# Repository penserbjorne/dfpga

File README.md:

#dfpga

##Fork

- Fork de [Nick Johnson a.k.a. Arachnid](https://github.com/Arachnid/dfpga)
- Fuente del articulo en el [Blog de Nick](http://blog.notdot.net/2012/10/Build-your-own-FPGA)

##Descripción

Implementación de una celda (slice) de un FPGA completamente con lógica 
discreta (componentes de la serie 7400), y un compilador para un dialecto HDL
 personalizado para la misma.

- discretefpga.brd y discretefpga.sch son los archivos para la tarjeta y el 
  esquematico en Eagle.
- dhdl.py es el compilador HDL; para ejecutarlo ``python dhdl.py infile outfile``.
- Los archivos *.dhdl son scripts DHDL de ejemplo.

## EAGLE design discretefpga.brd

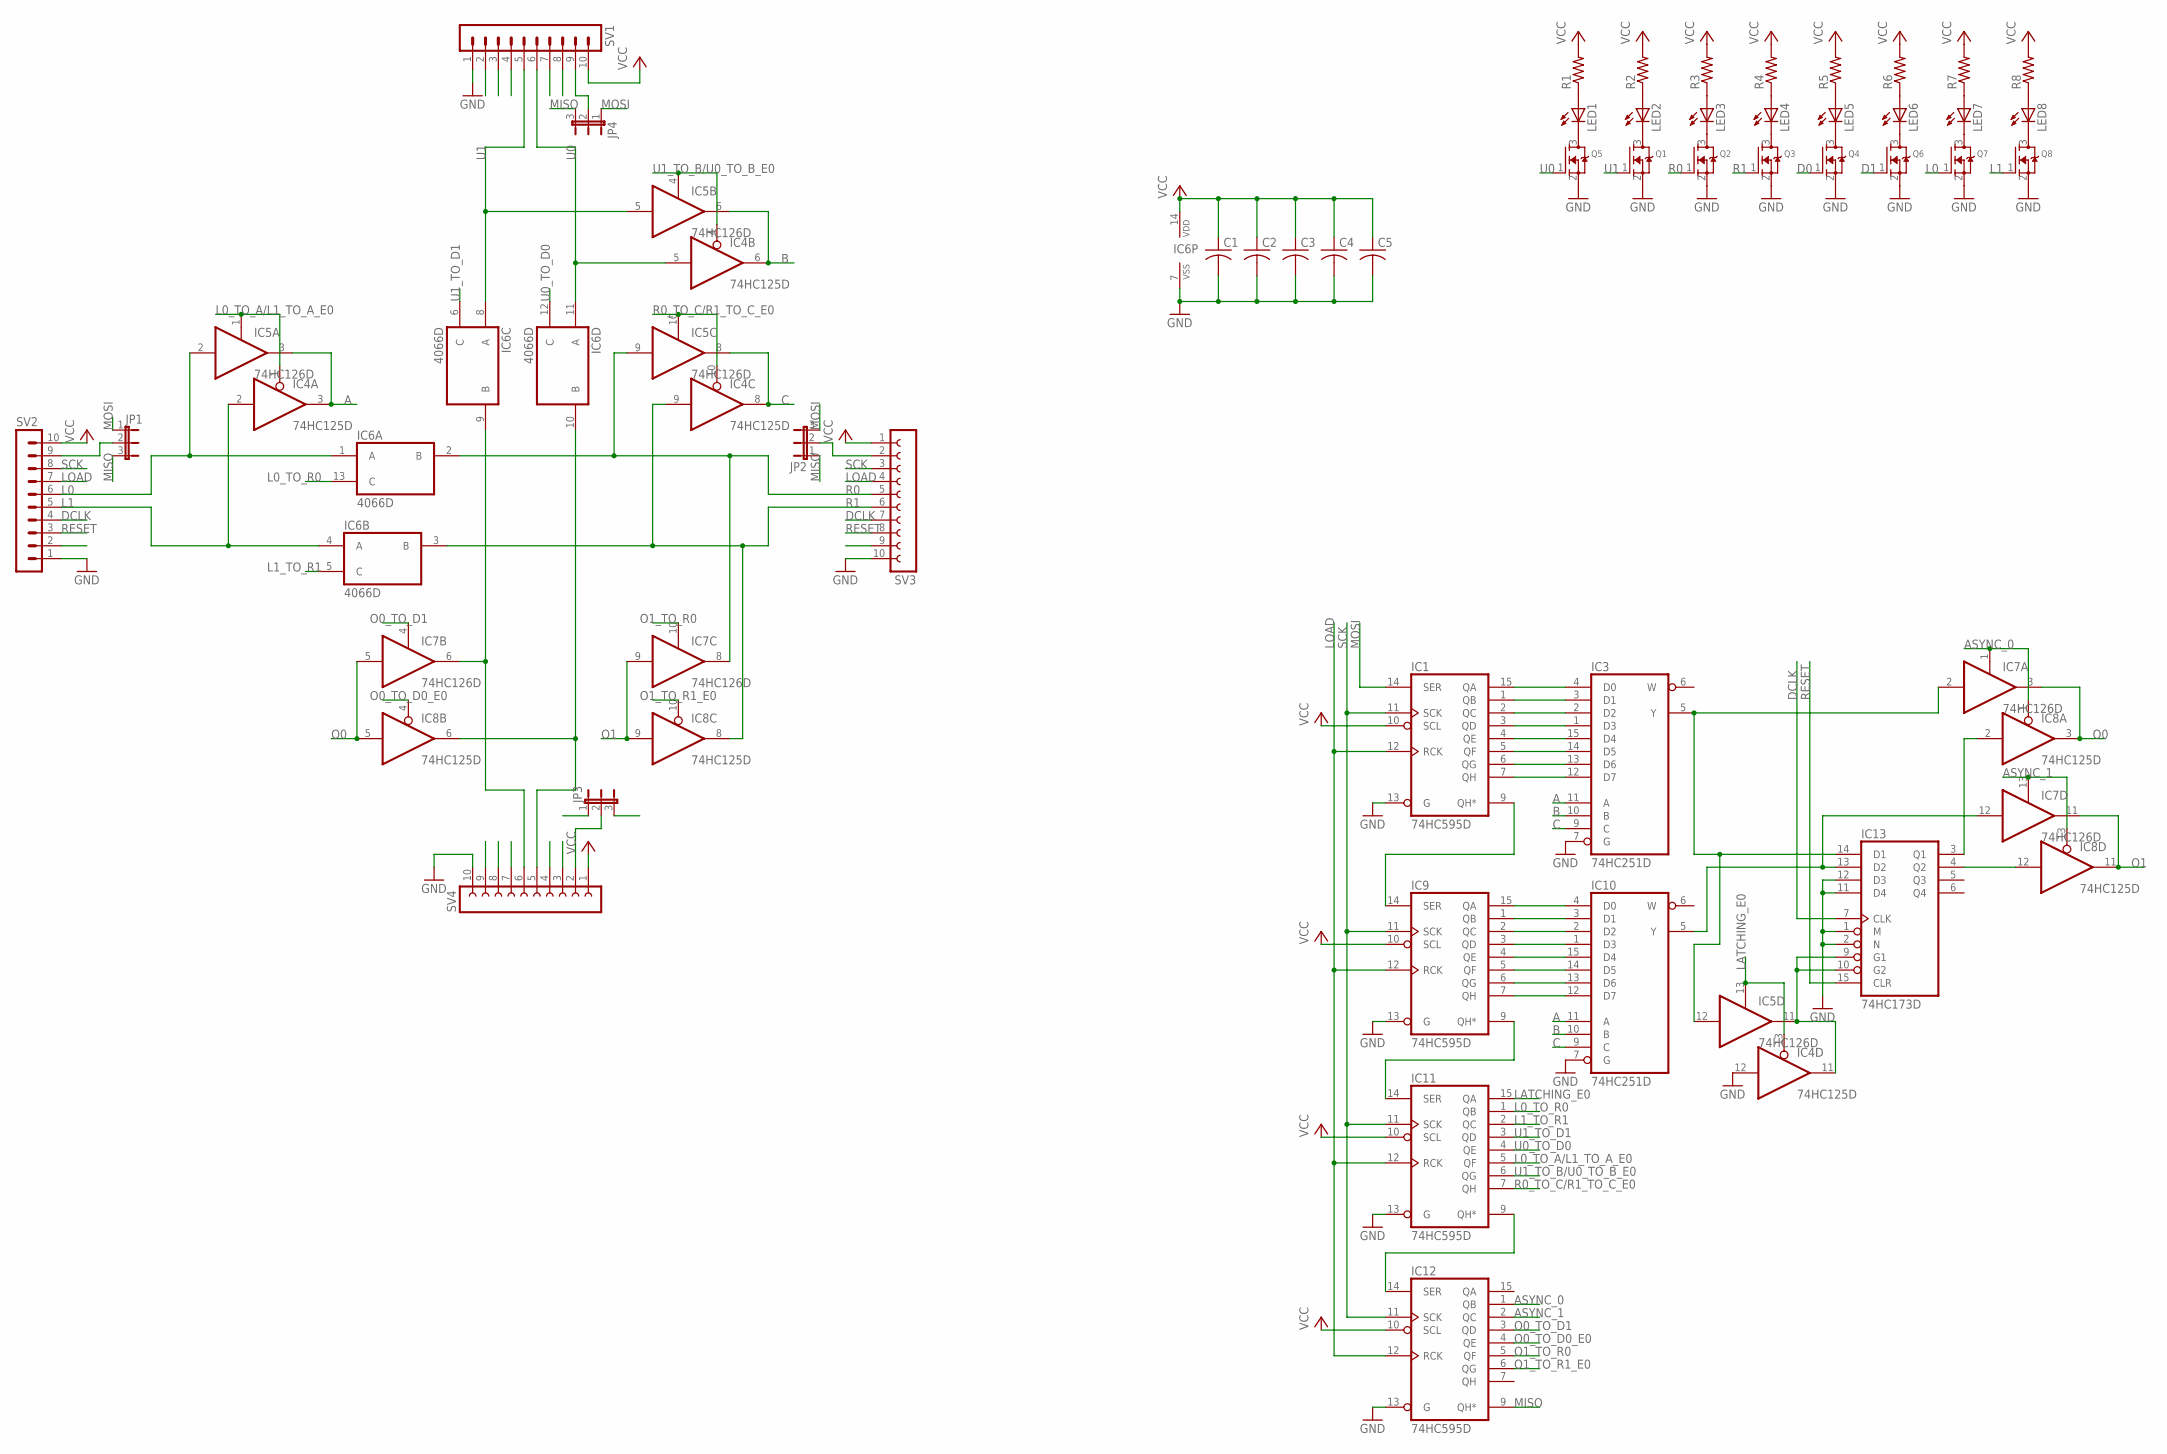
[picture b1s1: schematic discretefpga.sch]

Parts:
C1, C2, C3, C4, C5: C-USC0805; C0805
IC1, IC9, IC11, IC12: 74HC595D; SO16
IC3, IC10: 74HC251D; SO16
IC4, IC8: 74HC125D; SO14
IC5, IC7: 74HC126D; SO14
IC6: 4066D; SO14
IC13: 74HC173D; SO16
JP1, JP2, JP3, JP4: JP2E; JP2
LED1, LED2, LED3, LED4, LED5, LED6, LED7, LED8: LEDCHIP-LED0805; CHIP-LED0805
Q1, Q2, Q3, Q4, Q5, Q6, Q7, Q8: MOSFET-NREFLOW; SOT23
R1, R2, R3, R4, R5, R6, R7, R8: R-US_R0805; R0805
SV1, SV2: MA10-1W
SV3, SV4: FE10W

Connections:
A: IC3.11 (A), IC4.3 (O), IC5.3 (O), IC10.11 (A)
ASYNC_0: IC7.1 (OE), IC8.1 (OE), IC12.1 (QB)
ASYNC_1: IC7.13 (OE), IC8.13 (OE), IC12.2 (QC)
B: IC3.10 (B), IC4.6 (O), IC5.6 (O), IC10.10 (B)
C: IC3.9 (C), IC4.8 (O), IC5.8 (O), IC10.9 (C)
D0: IC6.10 (B), IC8.6 (O), Q4.1 (G), SV4.5
D1: IC6.9 (B), IC7.6 (O), Q6.1 (G), SV4.6
DCLK: IC13.7 (CLK), SV1.4, SV2.4, SV3.7, SV4.7
GND: C1.2, C2.2, C3.2, C4.2, C5.2, IC1.8 (GND), IC1.13 (G), IC3.7 (G), IC3.8 (GND), IC4.7 (GND), IC4.12 (I), IC5.7 (GND), IC6.7 (VSS), IC7.7 (GND), IC8.7 (GND), IC9.8 (GND), IC9.13 (G), IC10.7 (G), IC10.8 (GND), IC11.8 (GND), IC11.13 (G), IC12.8 (GND), IC12.13 (G), IC13.1 (M), IC13.2 (N), IC13.8 (GND), IC13.11 (D4), IC13.12 (D3), Q1.2 (S), Q2.2 (S), Q3.2 (S), Q4.2 (S), Q5.2 (S), Q6.2 (S), Q7.2 (S), Q8.2 (S), SV1.1, SV2.1, SV3.10, SV4.10
L0: IC5.2 (I), IC6.1 (A), Q7.1 (G), SV2.6
L0_TO_A/L1_TO_A_E0: IC4.1 (OE), IC5.1 (OE), IC11.5 (QF)
L0_TO_R0: IC6.13 (C), IC11.1 (QB)
L1: IC4.2 (I), IC6.4 (A), Q8.1 (G), SV2.5
L1_TO_R1: IC6.5 (C), IC11.2 (QC)
LATCHING_E0: IC4.13 (OE), IC5.13 (OE), IC11.15 (QA)
LOAD: IC1.12 (RCK), IC9.12 (RCK), IC11.12 (RCK), IC12.12 (RCK), SV1.7, SV2.7, SV3.4, SV4.4
MISO: IC12.9 (QH*), JP1.3, JP2.1, JP3.1, JP4.3
MOSI: IC1.14 (SER), JP1.1, JP2.3, JP3.3, JP4.1
unnamed: IC1.15 (QA), IC3.4 (D0)
unnamed: IC1.1 (QB), IC3.3 (D1)
unnamed: IC1.2 (QC), IC3.2 (D2)
unnamed: IC1.4 (QE), IC3.15 (D4)
unnamed: IC1.5 (QF), IC3.14 (D5)
unnamed: IC1.6 (QG), IC3.13 (D6)
unnamed: IC1.7 (QH), IC3.12 (D7)
unnamed: IC3.5 (Y), IC5.12 (I), IC7.2 (I), IC13.14 (D1)
unnamed: IC9.15 (QA), IC10.4 (D0)
unnamed: IC4.11 (O), IC5.11 (O), IC13.9 (G1), IC13.10 (G2)
unnamed: IC9.1 (QB), IC10.3 (D1)
unnamed: IC9.2 (QC), IC10.2 (D2)
unnamed: IC9.4 (QE), IC10.15 (D4)
unnamed: IC9.5 (QF), IC10.14 (D5)
unnamed: IC9.6 (QG), IC10.13 (D6)
unnamed: IC9.7 (QH), IC10.12 (D7)
unnamed: IC7.12 (I), IC10.5 (Y), IC13.13 (D2)
unnamed: IC1.9 (QH*), IC9.14 (SER)
unnamed: IC8.2 (I), IC13.3 (Q1)
unnamed: IC9.9 (QH*), IC11.14 (SER)
unnamed: IC11.9 (QH*), IC12.14 (SER)
unnamed: JP1.2, SV2.9
unnamed: JP2.2, SV3.2
unnamed: LED1.A, R1.1
unnamed: LED1.C, Q5.3 (D)
unnamed: IC8.12 (I), IC13.4 (Q2)
unnamed: IC9.3 (QD), IC10.1 (D3)
unnamed: IC1.3 (QD), IC3.1 (D3)
unnamed: LED2.C, Q1.3 (D)
unnamed: LED2.A, R2.1
unnamed: LED3.A, R3.1
unnamed: LED4.A, R4.1
unnamed: LED5.A, R5.1
unnamed: LED6.A, R6.1
unnamed: LED7.A, R7.1
unnamed: LED8.A, R8.1
unnamed: LED3.C, Q2.3 (D)
unnamed: LED4.C, Q3.3 (D)
unnamed: LED5.C, Q4.3 (D)
unnamed: JP3.2, SV4.2
unnamed: LED6.C, Q6.3 (D)
unnamed: JP4.2, SV1.9
unnamed: LED7.C, Q7.3 (D)
unnamed: LED8.C, Q8.3 (D)
O0: IC7.3 (O), IC7.5 (I), IC8.3 (O), IC8.5 (I)
O0_TO_D0_E0: IC8.4 (OE), IC12.4 (QE)
O0_TO_D1: IC7.4 (OE), IC12.3 (QD)
O1: IC7.9 (I), IC7.11 (O), IC8.9 (I), IC8.11 (O)
O1_TO_R0: IC7.10 (OE), IC12.5 (QF)
O1_TO_R1_E0: IC8.10 (OE), IC12.6 (QG)
R0: IC5.9 (I), IC6.2 (B), IC7.8 (O), Q2.1 (G), SV3.5
R0_TO_C/R1_TO_C_E0: IC4.10 (OE), IC5.10 (OE), IC11.7 (QH)
R1: IC4.9 (I), IC6.3 (B), IC8.8 (O), Q3.1 (G), SV3.6
RESET: IC13.15 (CLR), SV1.3, SV2.3, SV3.8, SV4.8
SCK: IC1.11 (SCK), IC9.11 (SCK), IC11.11 (SCK), IC12.11 (SCK), SV1.8, SV2.8, SV3.3, SV4.3
U0: IC4.5 (I), IC6.11 (A), Q5.1 (G), SV1.6
U0_TO_D0: IC6.12 (C), IC11.4 (QE)
U1: IC5.5 (I), IC6.8 (A), Q1.1 (G), SV1.5
U1_TO_B/U0_TO_B_E0: IC4.4 (OE), IC5.4 (OE), IC11.6 (QG)
U1_TO_D1: IC6.6 (C), IC11.3 (QD)
VCC: C1.1, C2.1, C3.1, C4.1, C5.1, IC1.10 (SCL), IC1.16 (VCC), IC3.16 (VCC), IC4.14 (VCC), IC5.14 (VCC), IC6.14 (VDD), IC7.14 (VCC), IC8.14 (VCC), IC9.10 (SCL), IC9.16 (VCC), IC10.16 (VCC), IC11.10 (SCL), IC11.16 (VCC), IC12.10 (SCL), IC12.16 (VCC), IC13.16 (VCC), R1.2, R2.2, R3.2, R4.2, R5.2, R6.2, R7.2, R8.2, SV1.10, SV2.10, SV3.1, SV4.1

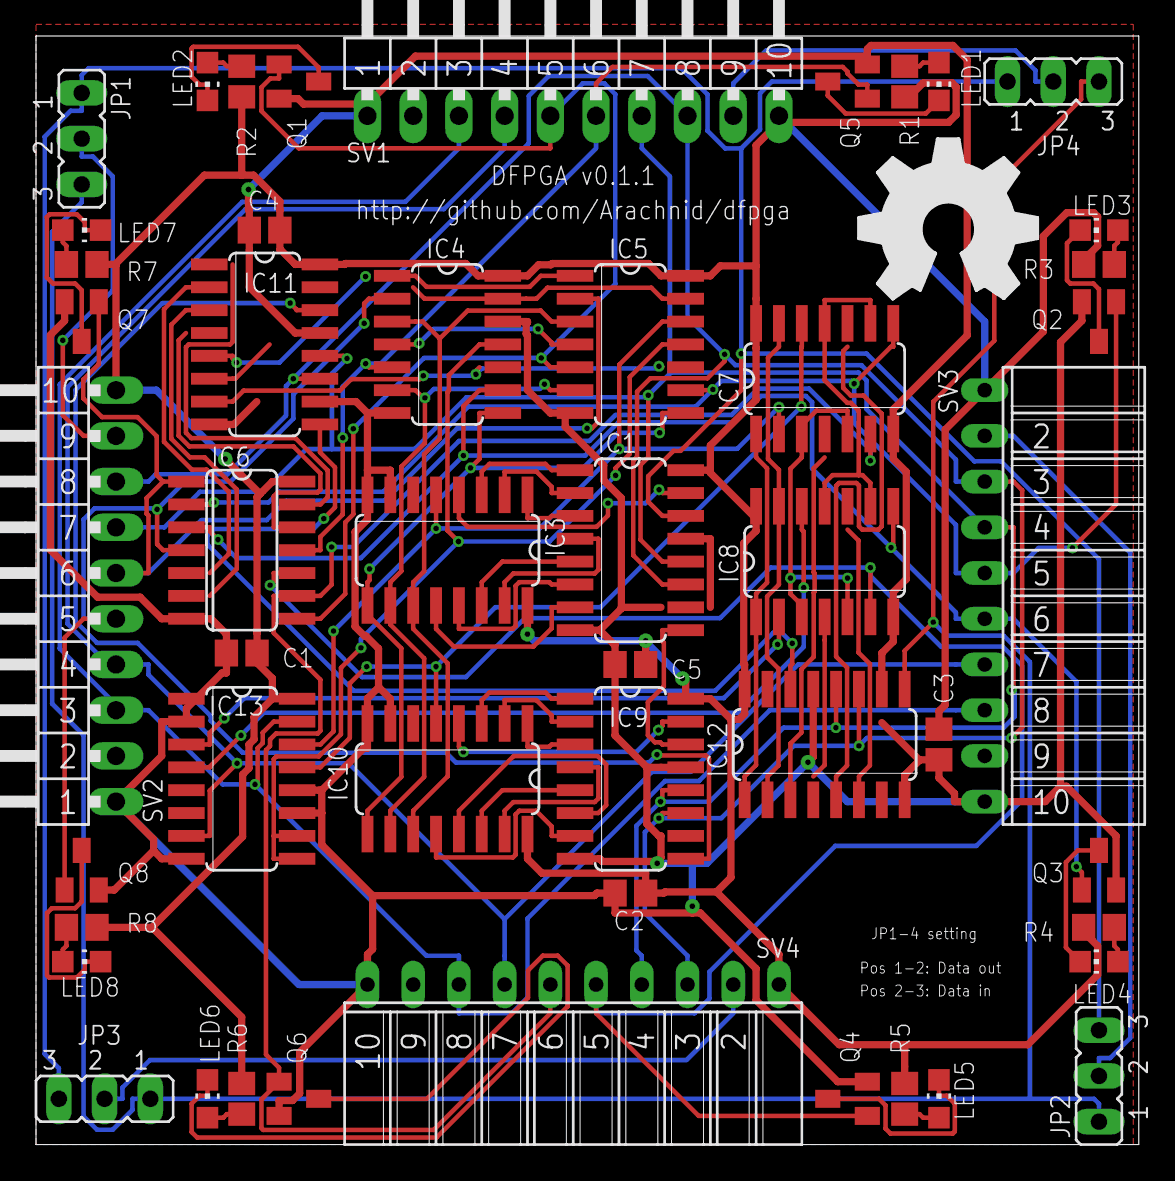
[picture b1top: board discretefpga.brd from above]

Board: 2 copper layers, 61.3 x 61.6 mm, 50 parts (0 on the bottom side), 79 nets.

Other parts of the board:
U$1: OSHW_FILLX350_NOTEXT

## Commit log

2016-12-03 Update README.md
    Se cambio la información a español.
2016-12-07 Se añade programa control en arduino
2016-12-07 Se reacomodaron los pines para un mejor uso.
2016-12-07 Se añade estructura base para el reporte.
2016-12-07 Se añadio la teoria en la documentacion
2016-12-07 updated schematic
2016-12-07 Se añade metodo de solucion, implementacion virtual, codigo de arduino.
2016-12-07 Se añade estilo al codigo de arduino en latex.
2016-12-07 Se añade referencias.
2016-12-07 Se añade referencia al repo
2016-12-07 Se actualizo el programa en arduino. Se añadio la descripcion de pines
2016-12-07 Se actualizo el programa en arduino.
2016-12-07 Se añadio el excel
